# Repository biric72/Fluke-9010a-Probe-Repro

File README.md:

# Fluke-9010a-Probe-Repro-Package
 Fluke 9000A Probe Repro Project for the 9010A Microsystem Troubleshooter

Since these have become virtually unobtainable, I decided to try my best to make a repro which is as close as possible to the original’s physical appearance and electrical layout.

This project includes

- Gerber archive to order the PCB’s with your manufacturer of choice
- The KiCAD files of the board if you want to make any changes
- Freecad file of the probe’s case:
    - I tried to keep the the case as close as possible to the original, but also printable with a ‚normal‘ 3d printer (see manual) so internally it is a bit simplified.
    - not all sketches are fully constraint, I did not want to spent an unnecessary amount of time.
    - I printed the case with black PLA, the windows with clear/natural PLA and the cable guide with flexible TPU which worked quite well. 
- A build manual which includes a BOM and part numbers for DigiKey.

To complete the build you will need moderate SMD soldering and tinkering skills as well as a bit of patience.

Of course I cannot be responsible  for any damage you do to yourself or your fluke mainframe; however, I have built 2 probes and they seem to work flawlessly.

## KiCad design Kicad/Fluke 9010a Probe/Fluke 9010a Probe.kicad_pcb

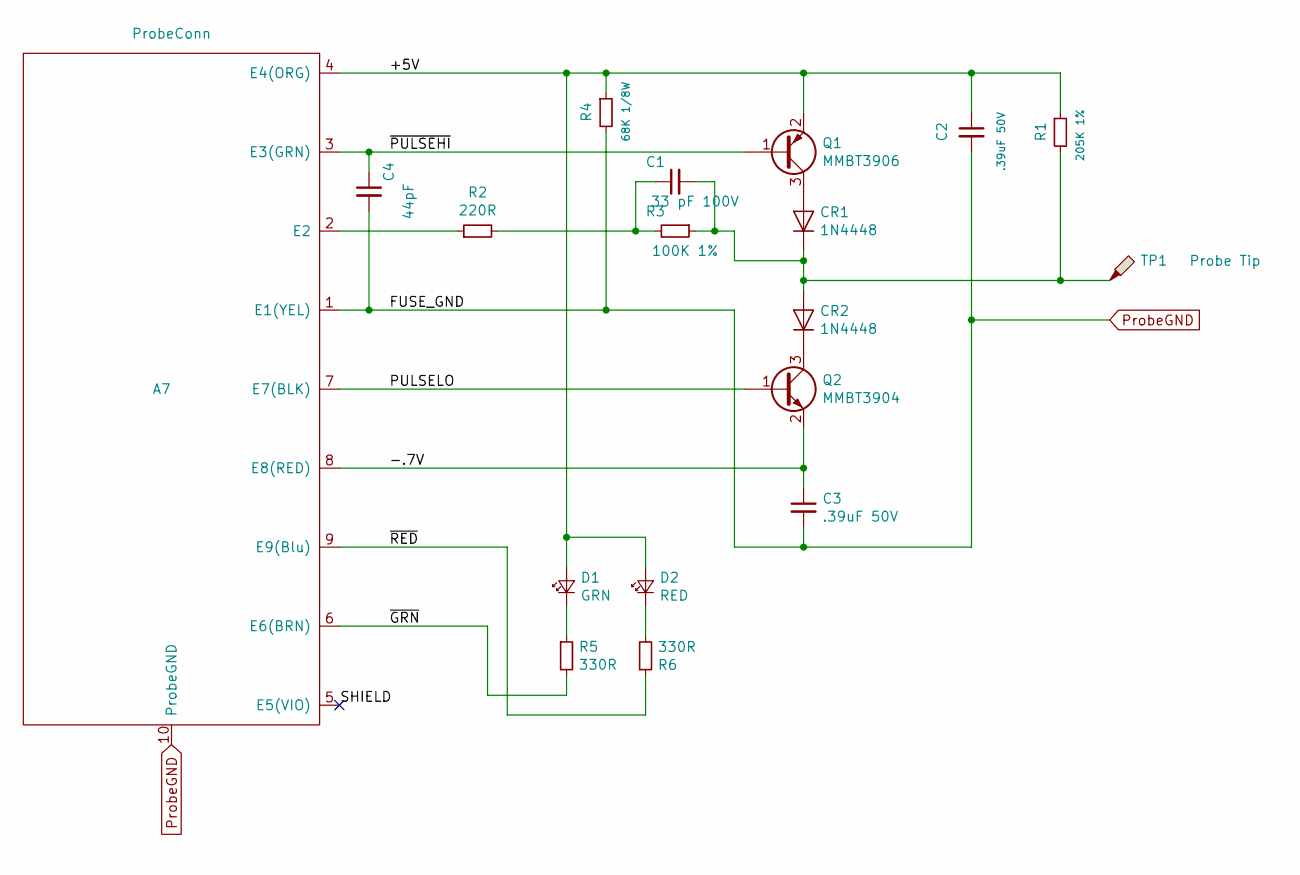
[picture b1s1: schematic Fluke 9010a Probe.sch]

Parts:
A7: ProbeConn; FlukeProbe_9Pin_3
C1: 33 pF 100V; C_0805_2012Metric_Pad1.15x1.40mm_HandSolder
C2, C3: .39uF 50V; C_0805_2012Metric_Pad1.15x1.40mm_HandSolder
C4: 44pF; C_0805_2012Metric_Pad1.15x1.40mm_HandSolder
CR1, CR2: 1N4448; D_1806_4516Metric
D1: GRN; LED_D3.0mm
D2: RED; LED_D3.0mm
Q1: MMBT3906; SOT-23_Handsoldering
Q2: MMBT3904; SOT-23_Handsoldering
R1: 205K 1%; D_0805_2012Metric_Pad1.15x1.40mm_HandSolder
R2: 220R; D_0805_2012Metric_Pad1.15x1.40mm_HandSolder
R3: 100K 1%; D_0805_2012Metric_Pad1.15x1.40mm_HandSolder
R4: 68K 1/8W; D_0805_2012Metric_Pad1.15x1.40mm_HandSolder
R5, R6: 330R; D_0805_2012Metric_Pad1.15x1.40mm_HandSolder
TP1: Probe Tip; TestPoint_THTPad_3.0x3.0mm_Drill1.5mm

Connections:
/+5V: A7.4 (E4(ORG)), C2.1, D1.2 (A), D2.2 (A), Q1.2 (E), R1.1, R4.1
/-.7V: A7.8 (E8(RED)), C3.1, Q2.2 (E)
/PULSELO: A7.7 (E7(BLK)), Q2.1 (B)
/SHIELD: A7.5 (E5(VIO))
/~GRN: A7.6 (E6(BRN)), R5.2
/~PULSEHI: A7.3 (E3(GRN)), C4.1, Q1.1 (B)
/~RED: A7.9 (E9(Blu)), R6.1
unnamed: A7.2 (E2), R2.1
unnamed: C1.1, R2.2, R3.2
unnamed: C1.2, CR1.1 (K), CR2.2 (A), R1.2, R3.1, TP1.1
unnamed: CR1.2 (A), Q1.3 (C)
unnamed: CR2.1 (K), Q2.3 (C)
unnamed: D1.1 (K), R5.1
unnamed: D2.1 (K), R6.2
ProbeGND: A7.1 (E1(YEL)), A7.10 (ProbeGND), C2.2, C3.2, C4.2, R4.2

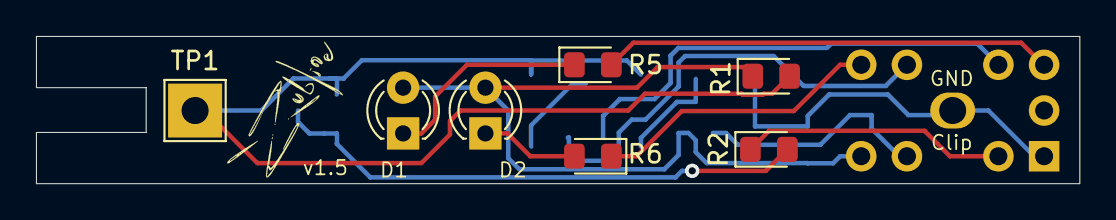
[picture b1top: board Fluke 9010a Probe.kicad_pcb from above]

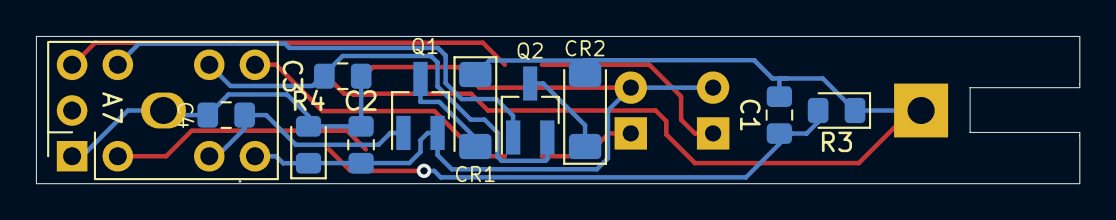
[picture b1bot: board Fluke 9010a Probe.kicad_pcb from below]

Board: 2 copper layers, 58.0 x 8.2 mm, 18 parts (11 on the bottom side), 14 nets.

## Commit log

2021-10-07 latest
